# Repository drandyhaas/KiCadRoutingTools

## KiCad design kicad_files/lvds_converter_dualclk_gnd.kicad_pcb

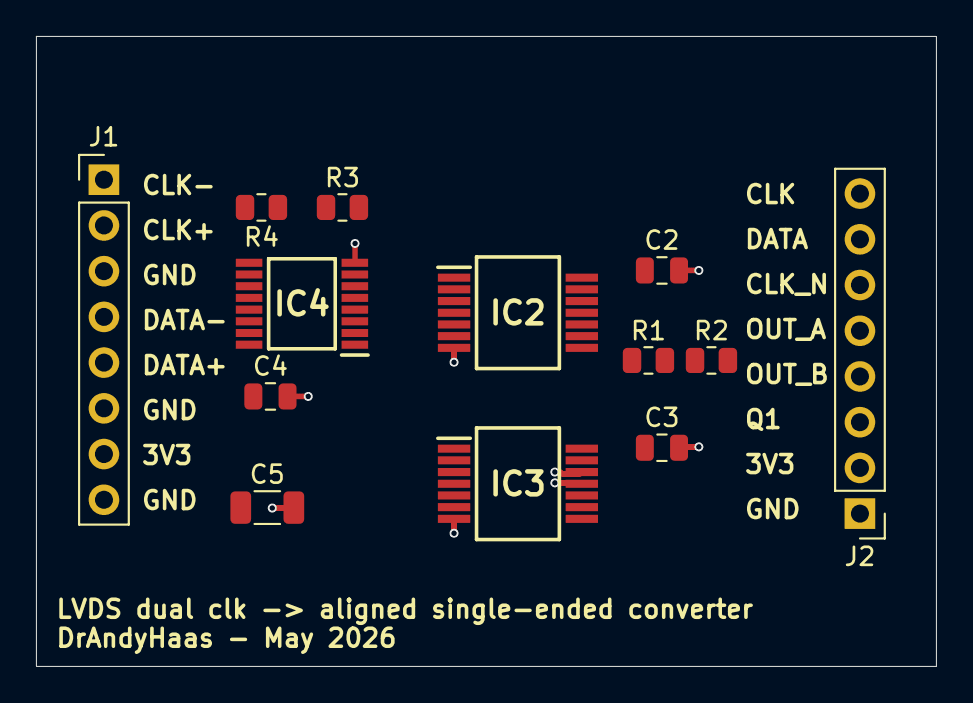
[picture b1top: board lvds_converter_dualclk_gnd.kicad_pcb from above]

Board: 2 copper layers, 50.0 x 35.0 mm, 13 parts (0 on the bottom side), 14 nets.

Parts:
C2, C3, C4: 0.1uF; C_0805_2012Metric
C5: 10uF; C_1206_3216Metric
IC2, IC3: SN74LVC74ADBR; SOP65P780X200-14N
IC4: DS90LV032ATMTCX_NOPB; SOP65P640X120-16N
J1, J2: Conn_01x08; PinHeader_1x08_P2.54mm_Vertical
R1, R2: 33; R_0805_2012Metric
R3, R4: 100; R_0805_2012Metric

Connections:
/CLK: IC3.3 (1CLK), IC4.3 (ROUT1), J2.8
/CLK+: IC4.2 (RIN1+), IC4.7 (RIN2-), J1.2, R3.1
/CLK-: IC4.1 (RIN1-), IC4.6 (RIN2+), J1.1, R3.2
/CLK_N: IC2.3 (1CLK), IC2.11 (2CLK), IC4.5 (ROUT2), J2.6
/DATA: IC2.2 (1D), IC3.2 (1D), IC4.11 (ROUT3), J2.7
/DATA+: IC4.10 (RIN3+), J1.5, R4.1
/DATA-: IC4.9 (RIN3-), J1.4, R4.2
/GND: C2.2, C3.2, C4.2, C5.2, IC2.7 (GND), IC3.7 (GND), IC3.11 (2CLK), IC3.12 (2D), IC4.8 (GND), IC4.12 (EN_2), J1.3, J1.6, J1.8, J2.1
/OUT_A: IC2.9 (2Q), R2.1
/OUT_A_R: J2.5, R2.2
/OUT_B: IC2.5 (1Q), R1.1
/OUT_B_R: J2.4, R1.2
/Q1: IC2.12 (2D), IC3.5 (1Q), J2.3
/VCC: C2.1, C3.1, C4.1, C5.1, IC2.1 (1~CLR), IC2.4 (1~PRE), IC2.10 (2~PRE), IC2.13 (2~CLR), IC2.14 (VCC), IC3.1 (1~CLR), IC3.4 (1~PRE), IC3.10 (2~PRE), IC3.13 (2~CLR), IC3.14 (VCC), IC4.4 (EN_1), IC4.16 (VCC), J1.7, J2.2

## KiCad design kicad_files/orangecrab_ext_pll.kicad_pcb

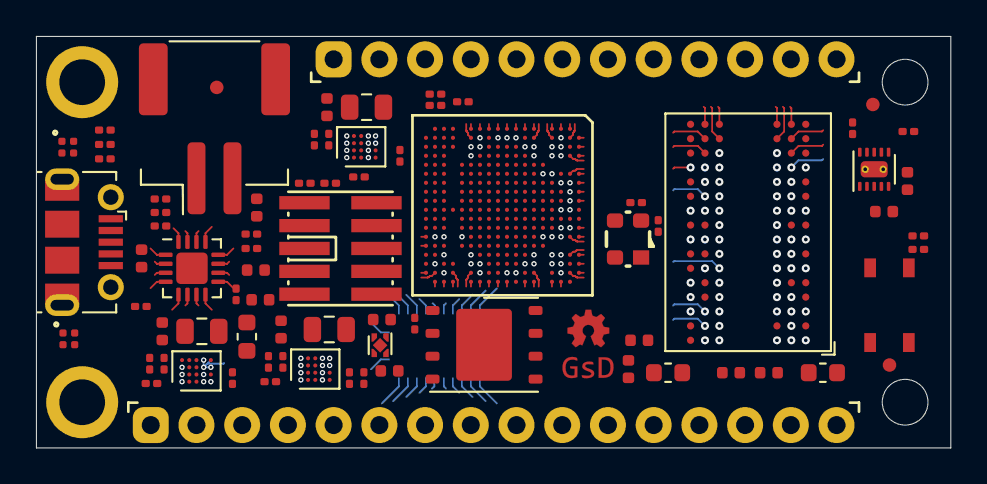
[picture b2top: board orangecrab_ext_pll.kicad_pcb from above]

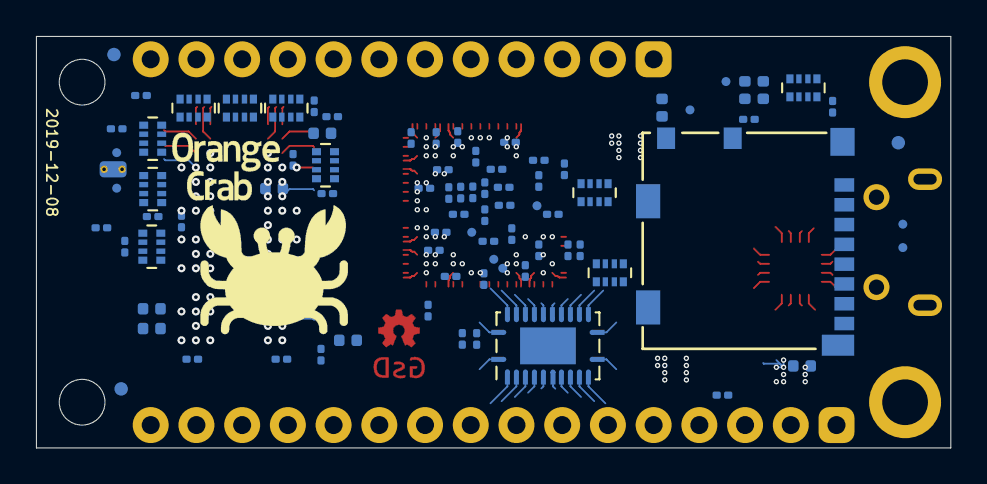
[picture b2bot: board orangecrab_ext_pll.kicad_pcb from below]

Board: 6 copper layers, 50.8 x 22.9 mm, 164 parts (83 on the bottom side), 154 nets.

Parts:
C1, C2, C5, C14, C19, C25, C27, C38, C40, C42, C44, C45, C48, C49, C52, C53, C56, C58, C60, C62, C63, C66, C67, C74, C76: 10nF; C_0201_0603Metric
C3: 10uF; C_0603_1608Metric
C4, C9, C20, C26, C28, C30, C31, C32, C33, C39, C41, C43, C50, C51, C54, C55, C57, C59, C61, C64, C65, C68, C69, C70, C71, C75: 100nF; C_0201_0603Metric
C6, C7, C8, C11, C15, C16, C17, C18, C29: 10uF; C_0402_1005Metric
C10: 0.22uF; C_0201_0603Metric
C12, C13, C46, C47, C77: 4.7uF; C_0402_1005Metric
C21, C22, C34, C35, C36, C37: 1uF; C_0402_1005Metric
C23, C24: 22uF; C_0603_1608Metric
D1, D2: LED_ARGB; 0404LED_RGB
FB1, FB2, FB3: 600R; L_0402_1005Metric
FID1, FID2, FID3, FID4, FID5, FID6: Fiducial; Fiducial_0.75mm_Mask1.5mm
H1, H2: MountingHole; MountingHole_2.2mm_M2_Pad
H3, H4: MountingHole; MountingHole_2.1mm
J1: Conn_01x12_Male; Feather_PinHeader_1x12
J2: Conn_01x16_Male; Feather_PinHeader_1x16
J3: USB_B_Micro; USB_Micro-B_Molex-105017-0001
J4: MicroSd; molex_microsd_1040310811
J5: JST; JST_PH_B2B-PH-SM4-TB_1x02-1MP_P2.00mm_Vertical
J6: JTAG; FTSH-105-XX-X-DV
L1, L2, L3: 0.47uH; L_0805_2012Metric
OSC1: KC2520B48.0000C10E00; Oscilator_2.5x2.0
R1, R5, R13, R14, R17, R18, R25: 100k; R_0201_0603Metric
R2: 31.6k; R_0201_0603Metric
R3, R6: 50R; R_0201_0603Metric
R4, R8, R23, R27, R30: 4.7k; R_0201_0603Metric
R7, R26, R28, R32, R33: 10k; R_0201_0603Metric
R9, R24: 3.57k; R_0201_0603Metric
R10: 56.2k; R_0201_0603Metric
R11: 3.06k; R_0201_0603Metric
R12: 4.32k; R_0201_0603Metric
R15: 267k; R_0201_0603Metric
R16: 147k; R_0201_0603Metric
R19: 240R; R_0402_1005Metric
R20, R22, R31: 1.5k; R_0201_0603Metric
R21, R29: 20R; R_0201_0603Metric
RN1, RN2, RN3, RN4, RN5, RN6, RN8, RN10: 50R; R_Array_Convex_4x0402
RN7, RN9: 10K; R_Array_Convex_4x0402
SW1: SW_Push; PTS_810_SMT_Switch
TP19, TP20, TP26, TP27, TP28, TP29, TP30, TP31, TP32, TP33: SMD_TP; TestPoint_Pad_D0.5mm
U1, U2, U7: FAN53541; WLCSP-20_1.934x2.434mm_Layout4x5_P0.4mm
U3: LFE5U-25F-8MG285C; csBGA_132
U4: MT41K64M16TW-107_J-TR; BGA-96_9.0x13.0mm_Layout2x3x16_P0.8mm
U5: BQ24232; QFN-16-1EP_3x3mm_P0.5mm_EP1.75x1.75mm
U6: W25Q128JVP; WSON-8-1EP_6x5mm_P1.27mm_EP3.4x4mm
U8: TPS51206; WSON-10-1EP_2x2mm_P0.4mm
U9: 74HC4067BQ; Texas_RGY_R-PVQFN-N24_EP2.05x3.1mm
U10: NCP115-2.5; Texas_X2SON-4_1x1mm_P0.65mm

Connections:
/sheetHyperRAM/RAM_VDD: C21.1, C23.1, C30.1, C32.1, C34.1, C36.1, FB2.1, U4.B2, U4.D9, U4.G7, U4.K2, U4.K8, U4.N1, U4.N9, U4.R1, U4.R9
/sheetHyperRAM/RAM_VDDQ: C22.1, C24.1, C31.1, C33.1, C35.1, C37.1, FB3.1, U4.A1, U4.A8, U4.C1, U4.C9, U4.D2, U4.E9, U4.F1, U4.H2, U4.H9
/sheetHyperRAM/RAM_ZQ: R19.1, U4.L8
/sheetIO/A0: J2.5, RN10.8, U9.8
/sheetIO/A1: J2.6, RN10.7, U9.7
/sheetIO/A2: J2.7, RN10.6, U9.6
/sheetIO/A3: J2.8, RN10.5, U9.5
/sheetIO/A4: J2.9, R6.1, U9.4
/sheetIO/A5: J2.10, R3.1, U9.3
/sheetIO/AREF: C71.1, J2.3, U9.2
/sheetIO/_USB_D_N: J3.2, R29.2, TP27.1
/sheetIO/_USB_D_P: J3.3, R21.1, TP26.1
/sheetPower/PGOOD_P1.1V: R13.1, U1.A1, U2.A2, U7.A2, U10.3
/sheetPower/PGOOD_P1.35V: R14.1, U7.A1, U8.7, U8.9
/sheetPower/PGOOD_P3.3V: R1.1, U2.A1
ADC_CTRL0: RN9.3, RN9.4, U3.G1
ADC_CTRL1: U3.F1, U9.15
ADC_MUX0: U3.F4, U9.10
ADC_MUX1: U3.F3, U9.11
ADC_MUX2: U3.F2, U9.14
ADC_MUX3: U3.H1, U9.13
ADC_SENSE_HI: RN9.7, RN9.8, U3.H3
ADC_SENSE_LO: C28.1, RN9.5, RN9.6, U3.G3
ECP5_VREF: C1.1, C4.1, C10.2, C19.1, C20.1, C25.1, C26.1, C44.2, C45.2, TP28.1, U3.B4, U3.C15, U3.H15, U4.H1, U4.M8, U8.6
EN: J1.2, R25.1, U1.A2
EXT_PLL+: TP19.1, U3.M16
EXT_PLL-: TP20.1, U3.M17
FPGA_RESET: J2.1, J6.10, U3.T15, U3.V17
GND: C1.2, C2.1, C3.1, C4.2, C5.1, C6.1, C7.1, C8.1, C9.1, C10.1, C11.1, C12.2, C13.2, C14.1, C15.1, C16.1, C17.1, C18.1, C19.2, C20.2, C21.2, C22.2, C23.2, C24.2, C25.2, C26.2, C28.2, C29.1, C30.2, C31.2, C32.2, C33.2, C34.2, C35.2, C36.2, C37.2, C38.1, C39.1, C40.1, C41.1, C42.1, C43.1, C44.1, C45.1, C46.2, C47.2, C48.2, C49.2, C50.2, C51.2, C52.2, C53.2, C54.2, C55.2, C56.2, C57.2, C58.2, C59.2, C60.2, C61.2, C62.2, C63.2, C64.2, C65.2, C66.2, C67.2, C68.2, C69.2, C70.1, C71.2, C74.2, C75.2, C76.2, C77.2, J2.4, J2.16, J3.5, J3.6, J4.6, J4.MP, J5.1, J5.MP, J6.3, J6.5, J6.7, J6.9, OSC1.2, R2.2, R9.1, R10.1, R11.1, R12.1, R15.2, R16.2, R19.2, R26.1, R27.1, R33.2, RN9.2, SW1.1, U1.B1, U1.B2, U1.B3, U1.B4, U1.C1, U1.C2, U1.C3, U1.C4, U2.B1, U2.B2, U2.B3, U2.B4, U2.C1, U2.C2, U2.C3, U2.C4, U3.B3, U3.B16, U3.E5, U3.E7, U3.E8, U3.E9, U3.E10, U3.E11, U3.E12, U3.E14, U3.F5, U3.F6, U3.F7, U3.F8, U3.F9, U3.F10, U3.F11, U3.F12, U3.F13, U3.F14, U3.G2, U3.G6, U3.G7, U3.G8, U3.G9, U3.G10, U3.G11, U3.G12, U3.G13, U3.G17, U3.H6, U3.H7, U3.H8, U3.H9, U3.H10, U3.H11, U3.H12, U3.H13, U3.J6, U3.J7, U3.J8, U3.J9, U3.J10, U3.J11, U3.J12, U3.J13, U3.K5, U3.K6, U3.K7, U3.K8, U3.K9, U3.K10, U3.K11, U3.K12, U3.K13, U3.K14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
IO_0: J2.14, U3.N17
IO_1: J2.15, U3.M18
IO_5: J1.10, U3.B10
IO_6: J1.9, U3.B9
IO_9: J1.8, U3.C8
IO_10: J1.7, U3.B8
IO_11: J1.6, U3.A8
IO_12: J1.5, U3.H2
IO_13: J1.4, U3.J2
IO_A0: RN10.1, U3.L4
IO_A1: RN10.2, U3.N3
IO_A2: RN10.3, U3.N4
IO_A3: RN10.4, U3.H4
IO_A4: R6.2, U3.G4
IO_A5: R3.2, U3.T17
IO_MISO: J2.13, U3.N15
IO_MOSI: J2.12, U3.N16
IO_SCK: J2.11, U3.R17
IO_SCL: J1.11, U3.C9
IO_SDA: J1.12, U3.C10
JTAG_TCK: J6.4, R27.2, U3.U13
JTAG_TDI: J6.8, U3.T13
JTAG_TDO: J6.6, U3.V14
JTAG_TMS: J6.2, U3.V13
LED_B: R24.1, U3.J3
LED_G: R23.1, U3.M3
LED_R: R22.1, U3.K4
unnamed: C27.1, RN6.3, RN6.4
unnamed: C29.2, C70.2, FB1.1, J4.4
unnamed: D1.2, R22.2
unnamed: D1.3, R23.2
unnamed: D1.4, R24.2
unnamed: D2.2, R8.2
unnamed: D2.3, R7.2
unnamed: L1.1, U1.D3, U1.D4, U1.E3, U1.E4
unnamed: L2.1, U2.D3, U2.D4, U2.E3, U2.E4
unnamed: L3.1, U7.D3, U7.D4, U7.E3, U7.E4
unnamed: R2.1, R5.2, U2.A3
unnamed: R7.1, U5.7
unnamed: R8.1, U5.9
unnamed: R9.2, U5.15
unnamed: R10.2, U5.14
unnamed: R11.2, U5.12
unnamed: R12.2, U5.16
unnamed: R15.1, R17.2, U1.A3
unnamed: R16.1, R18.2, U7.A3
unnamed: R26.2, U5.1
unnamed: R32.2, R33.1, U9.16
unnamed: RN9.1, U9.1
P1.1V: C15.2, C17.2, C48.1, C50.1, C52.1, C54.1, C56.1, C57.1, C58.1, C59.1, C60.1, C61.1, L1.2, R17.1, TP32.1, U1.A4, U3.D8, U3.D9, U3.D10, U3.D11, U3.J4, U3.J5, U3.J14, U3.J15, U3.M4, U3.M15, U3.P7, U3.P9, U3.P11, U9.17
P1.35V: C8.2, C16.2, C18.2, C62.1, C64.1, C66.1, C68.1, FB2.2, FB3.2, L3.2, R4.1, R18.1, TP31.1, U3.B18, U3.C6, U3.D17, U3.G5, U3.G14, U3.H5, U3.H14, U3.K15, U3.K16, U3.K17, U3.M14, U3.N14, U7.A4, U8.1, U8.2, U9.19
P2.5V: C47.1, C49.1, C51.1, C53.1, C55.1, TP30.1, U3.E6, U3.E13, U3.N6, U3.P13, U9.18, U10.1
P3.3V: C6.2, C7.2, C9.2, C46.1, C63.1, C65.1, C67.1, C69.1, C74.1, C75.1, D1.1, FB1.2, J2.2, J6.1, L2.2, OSC1.1, OSC1.4, R5.1, R28.1, R30.2, R31.2, RN7.5, RN7.6, RN7.7, RN7.8, TP29.1, U2.A4, U3.D7, U3.D12, U3.M5, U3.N5, U3.N13, U3.P14, U3.T14, U6.8, U8.10, U9.23, U9.24, U10.4
PUSB_VBUS: C77.1, J1.3, J3.1, U5.13
QSPI_D2: U3.R18, U6.3
QSPI_D3: U3.N18, U6.7
RAM_A0: RN5.6, U3.C4, U4.N3
RAM_A1: RN8.6, U3.D2, U4.P7
RAM_A2: RN5.8, U3.D3, U4.P3
RAM_A3: RN5.5, U3.A3, U4.N2
RAM_A4: RN1.7, U3.A4, U4.P8
RAM_A5: RN5.7, U3.D4, U4.P2
RAM_A6: RN1.6, U3.C3, U4.R8
RAM_A7: RN2.5, U3.B2, U4.R2
RAM_A8: RN1.5, U3.B1, U4.T8
RAM_A9: RN2.7, U3.D1, U4.R3
RAM_A10: RN8.5, U3.A7, U4.L7
RAM_A11: RN8.7, U3.C2, U4.R7
RAM_A12: RN1.8, U3.B6, U4.N7
RAM_A13: RN2.8, U3.C1, U4.T3
RAM_A14: RN8.8, U3.A2, U4.T7
RAM_A15: RN4.5, U3.C7, U4.M7
RAM_BA0: RN3.8, U3.D6, U4.M2
RAM_BA1: RN4.7, U3.B7, U4.N8
RAM_BA2: RN2.6, U3.A6, U4.M3
RAM_CAS#: RN3.5, U3.D13, U4.K3
RAM_CK+: RN6.6, U3.J18, U4.J7
RAM_CK-: RN6.5, U3.K18, U4.K7
RAM_CKE: RN4.8, U3.D18, U4.K9
RAM_CS#: RN3.6, U3.A12, U4.L2
RAM_D0: U3.C17, U4.E3
RAM_D1: U3.D15, U4.F7
RAM_D2: U3.B17, U4.F2
RAM_D3: U3.C16, U4.F8
RAM_D4: U3.A15, U4.H3
RAM_D5: U3.B13, U4.H8
RAM_D6: U3.A17, U4.G2
RAM_D7: U3.A13, U4.H7
RAM_D8: U3.F17, U4.D7
RAM_D9: U3.F16, U4.C3
RAM_D10: U3.G15, U4.C8
RAM_D11: U3.F15, U4.C2
RAM_D12: U3.J16, U4.A7
RAM_D13: U3.C18, U4.A2
RAM_D14: U3.H16, U4.B8
RAM_D15: U3.F18, U4.A3
RAM_LDM: U3.G16, U4.E7
RAM_LDQS+: U3.G18, U4.C7
RAM_LDQS-: U3.H17, U4.B7
RAM_ODT: RN6.8, U3.C13, U4.K1
RAM_RAS#: RN6.7, U3.C12, U4.J3
RAM_RESET#: U3.L18, U4.T2
RAM_UDM: U3.D16, U4.D3
RAM_UDQS+: U3.B15, U4.F3
RAM_UDQS-: U3.A16, U4.G3
RAM_WE#: RN3.7, U3.B12, U4.L3
REF_CLK: OSC1.3, U3.A9
SD0_CD: J4.9, R28.2, U3.L1
SD0_CLK: J4.5, U3.K1
SD0_CMD: J4.3, RN7.3, U3.K2
SD0_DAT0: J4.7, RN7.2, U3.J1
SD0_DAT1: J4.8, RN7.1, U3.K3
SD0_DAT2: J4.1, RN7.4, U3.L3
SD0_DAT3: J4.2, U3.M1
SPI_CONFIG_MISO: U3.T18, U6.2
SPI_CONFIG_MOSI: U3.U18, U6.5
SPI_CONFIG_SCK: R31.1, U3.U16, U6.6
SPI_CONFIG_SS: R30.1, U3.U17, U6.1
USB_D+: R20.1, R21.2, U3.N1
USB_D-: R29.1, U3.M2
USB_PULLUP: R20.2, U3.N2
USER_BUTTON: C76.1, R4.2, SW1.2, U3.J17
VBATT: C13.1, J1.1, J5.2, R32.1, U5.2, U5.3
VSYS: C2.2, C3.2, C5.2, C12.1, C14.2, D2.1, R1.2, R13.2, R14.2, R25.2, U1.D1, U1.D2, U1.E1, U1.E2, U2.D1, U2.D2, U2.E1, U2.E2, U5.5, U5.10, U5.11, U7.D1, U7.D2, U7.E1, U7.E2
VTT: C11.2, C27.2, C38.2, C39.2, C40.2, C41.2, C42.2, C43.2, RN1.1, RN1.2, RN1.3, RN1.4, RN2.1, RN2.2, RN2.3, RN2.4, RN3.1, RN3.2, RN3.3, RN3.4, RN4.1, RN4.2, RN4.3, RN4.4, RN5.1, RN5.2, RN5.3, RN5.4, RN6.1, RN6.2, RN8.1, RN8.2, RN8.3, RN8.4, TP33.1, U8.3, U8.5

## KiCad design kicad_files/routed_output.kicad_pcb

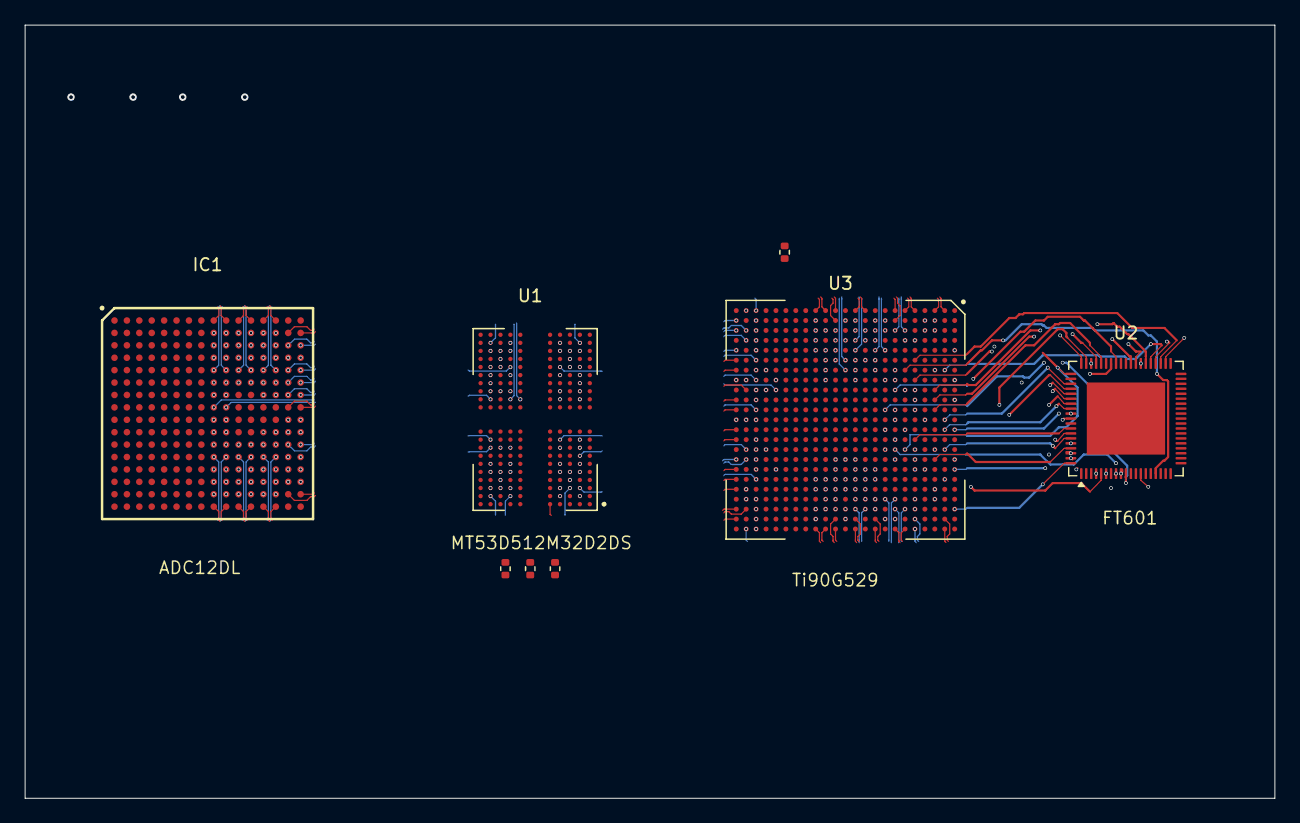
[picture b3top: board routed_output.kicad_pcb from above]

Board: 10 copper layers, 100.7 x 62.3 mm, 8 parts (0 on the bottom side), 228 nets.

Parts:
IC1: ADC12DL500ACF_Aligned; BGA256C100P16X16_1700X1700X331
R1, R2, R3, R4: 240; R_0402_1005Metric
U1: MT53D512M16D1DS_Aligned; IC_MT53D512M16D1DS-046_WT_D
U2: FT601Q_Aligned; QFN-76-1EP_9x9mm_P0.4mm_EP5.81x6.31mm
U3: Ti90G529_Functions; BGA-529_23x23_19.0x19.0mm

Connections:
/fpga_adc/VA11: IC1.E4 (VA11_1), IC1.E5 (VA11_2), IC1.E6 (VA11_3), IC1.F3 (VA11_4), IC1.F4 (VA11_5), IC1.F5 (VA11_6), IC1.F6 (VA11_7), IC1.L3 (VA11_8), IC1.L4 (VA11_9), IC1.L5 (VA11_10), IC1.L6 (VA11_11), IC1.M4 (VA11_12), IC1.M5 (VA11_13), IC1.M6 (VA11_14)
/fpga_adc/VA19: IC1.G3 (VA19_1), IC1.G4 (VA19_2), IC1.G5 (VA19_3), IC1.G6 (VA19_4), IC1.H3 (VA19_5), IC1.H4 (VA19_6), IC1.H5 (VA19_7), IC1.H6 (VA19_8), IC1.J3 (VA19_9), IC1.J4 (VA19_10), IC1.J5 (VA19_11), IC1.J6 (VA19_12), IC1.K3 (VA19_13), IC1.K4 (VA19_14), IC1.K5 (VA19_15), IC1.K6 (VA19_16)
/fpga_adc/VD11: IC1.E8 (VD11_1), IC1.F8 (VD11_2), IC1.G8 (VD11_3), IC1.K8 (VD11_4), IC1.L8 (VD11_5), IC1.M8 (VD11_6)
/fpga_adc/VLVDS: IC1.G11 (VLVDS_1), IC1.G12 (VLVDS_2), IC1.H11 (VLVDS_3), IC1.H12 (VLVDS_4), IC1.H13 (VLVDS_5), IC1.J11 (VLVDS_6), IC1.J12 (VLVDS_7), IC1.J13 (VLVDS_8), IC1.K11 (VLVDS_9), IC1.K12 (VLVDS_10)
/fpga_adc/lvds_rx1_1_N: IC1.T10 (DB0-), U3.E20 (lvds_rx1_1_N)
/fpga_adc/lvds_rx1_1_P: IC1.T9 (DB0+), U3.E21 (lvds_rx1_1)
/fpga_adc/lvds_rx1_2_N: IC1.R10 (DB1-), U3.P23 (lvds_rx1_2_N)
/fpga_adc/lvds_rx1_2_P: IC1.R9 (DB1+), U3.R23 (lvds_rx1_2)
/fpga_adc/lvds_rx1_3_N: IC1.P10 (DB2-), U3.R19 (lvds_rx1_3_N)
/fpga_adc/lvds_rx1_3_P: IC1.P9 (DB2+), U3.R18 (lvds_rx1_3)
/fpga_adc/lvds_rx1_4_N: IC1.N10 (DB3-), U3.P20 (lvds_rx1_4_N)
/fpga_adc/lvds_rx1_4_P: IC1.N9 (DB3+), U3.P21 (lvds_rx1_4)
/fpga_adc/lvds_rx1_5_N: IC1.M10 (DB4-), U3.N23 (lvds_rx1_5_N)
/fpga_adc/lvds_rx1_5_P: IC1.M9 (DB4+), U3.N22 (lvds_rx1_5)
/fpga_adc/lvds_rx1_6_N: IC1.L10 (DB5-), U3.P19 (lvds_rx1_6_N)
/fpga_adc/lvds_rx1_6_P: IC1.L9 (DB5+), U3.P18 (lvds_rx1_6)
/fpga_adc/lvds_rx1_7_N: IC1.T12 (DB6-), U3.L22 (lvds_rx1_7_N)
/fpga_adc/lvds_rx1_7_P: IC1.T11 (DB6+), U3.L23 (lvds_rx1_7)
/fpga_adc/lvds_rx1_8_N: IC1.R12 (DB7-), U3.N21 (lvds_rx1_8_N)
/fpga_adc/lvds_rx1_8_P: IC1.R11 (DB7+), U3.N20 (lvds_rx1_8)
/fpga_adc/lvds_rx1_9_N: IC1.P12 (DB8-), U3.N17 (lvds_rx1_9_N)
/fpga_adc/lvds_rx1_9_P: IC1.P11 (DB8+), U3.N16 (lvds_rx1_9)
/fpga_adc/lvds_rx1_10_N: IC1.N12 (DB9-), U3.N18 (lvds_rx1_10_N)
/fpga_adc/lvds_rx1_10_P: IC1.N11 (DB9+), U3.N19 (lvds_rx1_10)
/fpga_adc/lvds_rx1_11_N: IC1.M12 (DB10-), U3.M22 (lvds_rx1_11_N)
/fpga_adc/lvds_rx1_11_P: IC1.M11 (DB10+), U3.M21 (lvds_rx1_11)
/fpga_adc/lvds_rx1_12_N: IC1.L12 (DB11-), U3.H22 (lvds_rx1_12_N)
/fpga_adc/lvds_rx1_12_P: IC1.L11 (DB11+), U3.G22 (lvds_rx1_12)
/fpga_adc/lvds_rx1_13_N: IC1.J10 (DBSTR-), U3.M18 (lvds_rx1_13_N)
/fpga_adc/lvds_rx1_13_P: IC1.J9 (DBSTR+), U3.M19 (lvds_rx1_13)
/fpga_adc/lvds_rx2_1_N: IC1.T14 (DD0-), U3.K21 (lvds_rx2_1_N)
/fpga_adc/lvds_rx2_1_P: IC1.T13 (DD0+), U3.L21 (lvds_rx2_1)
/fpga_adc/lvds_rx2_2_N: IC1.R14 (DD1-), U3.G23 (lvds_rx2_2_N)
/fpga_adc/lvds_rx2_2_P: IC1.R13 (DD1+), U3.F23 (lvds_rx2_2)
/fpga_adc/lvds_rx2_3_N: IC1.P14 (DD2-), U3.M16 (lvds_rx2_3_N)
/fpga_adc/lvds_rx2_3_P: IC1.P13 (DD2+), U3.L16 (lvds_rx2_3)
/fpga_adc/lvds_rx2_4_N: IC1.N14 (DD3-), U3.E22 (lvds_rx2_4_N)
/fpga_adc/lvds_rx2_4_P: IC1.N13 (DD3+), U3.E23 (lvds_rx2_4)
/fpga_adc/lvds_rx2_5_N: IC1.M14 (DD4-), U3.J21 (lvds_rx2_5_N)
/fpga_adc/lvds_rx2_5_P: IC1.M13 (DD4+), U3.J20 (lvds_rx2_5)
/fpga_adc/lvds_rx2_6_N: IC1.L14 (DD5-), U3.L17 (lvds_rx2_6_N)
/fpga_adc/lvds_rx2_6_P: IC1.L13 (DD5+), U3.L18 (lvds_rx2_6)
/fpga_adc/lvds_rx2_7_N: IC1.K14 (DD6-), U3.F21 (lvds_rx2_7_N)
/fpga_adc/lvds_rx2_7_P: IC1.K13 (DD6+), U3.G21 (lvds_rx2_7)
/fpga_adc/lvds_rx2_8_N: IC1.R16 (DD7-), U3.K19 (lvds_rx2_8_N)
/fpga_adc/lvds_rx2_8_P: IC1.R15 (DD7+), U3.K20 (lvds_rx2_8)
/fpga_adc/lvds_rx2_9_N: IC1.P16 (DD8-), U3.L19 (lvds_rx2_9_N)
/fpga_adc/lvds_rx2_9_P: IC1.P15 (DD8+), U3.L20 (lvds_rx2_9)
/fpga_adc/lvds_rx2_10_N: IC1.N16 (DD9-), U3.J17 (lvds_rx2_10_N)
/fpga_adc/lvds_rx2_10_P: IC1.N15 (DD9+), U3.J18 (lvds_rx2_10)
/fpga_adc/lvds_rx2_11_N: IC1.M16 (DD10-), U3.B22 (lvds_rx2_11_N)
/fpga_adc/lvds_rx2_11_P: IC1.M15 (DD10+), U3.B23 (lvds_rx2_11)
/fpga_adc/lvds_rx2_12_N: IC1.L16 (DD11-), U3.K17 (lvds_rx2_12_N)
/fpga_adc/lvds_rx2_12_P: IC1.L15 (DD11+), U3.K18 (lvds_rx2_12)
/fpga_adc/lvds_rx2_13_N: IC1.J16 (DDSTR-), U3.G20 (lvds_rx2_13_N)
/fpga_adc/lvds_rx2_13_P: IC1.J15 (DDSTR+), U3.H20 (lvds_rx2_13)
/fpga_adc/lvds_rx3_1_N: IC1.A10 (DA0-), U3.C2 (lvds_rx3_1_N)
/fpga_adc/lvds_rx3_1_P: IC1.A9 (DA0+), U3.C3 (lvds_rx3_1)
/fpga_adc/lvds_rx3_2_N: IC1.B10 (DA1-), U3.R3 (lvds_rx3_2_N)
/fpga_adc/lvds_rx3_2_P: IC1.B9 (DA1+), U3.R2 (lvds_rx3_2)
/fpga_adc/lvds_rx3_3_N: IC1.C10 (DA2-), U3.P7 (lvds_rx3_3_N)
/fpga_adc/lvds_rx3_3_P: IC1.C9 (DA2+), U3.P8 (lvds_rx3_3)
/fpga_adc/lvds_rx3_4_N: IC1.D10 (DA3-), U3.R1 (lvds_rx3_4_N)
/fpga_adc/lvds_rx3_4_P: IC1.D9 (DA3+), U3.P1 (lvds_rx3_4)
/fpga_adc/lvds_rx3_5_N: IC1.E10 (DA4-), U3.P6 (lvds_rx3_5_N)
/fpga_adc/lvds_rx3_5_P: IC1.E9 (DA4+), U3.P5 (lvds_rx3_5)
/fpga_adc/lvds_rx3_6_N: IC1.F10 (DA5-), U3.N6 (lvds_rx3_6_N)
/fpga_adc/lvds_rx3_6_P: IC1.F9 (DA5+), U3.N5 (lvds_rx3_6)
/fpga_adc/lvds_rx3_7_N: IC1.A12 (DA6-), U3.P3 (lvds_rx3_7_N)
/fpga_adc/lvds_rx3_7_P: IC1.A11 (DA6+), U3.N3 (lvds_rx3_7)
/fpga_adc/lvds_rx3_8_N: IC1.B12 (DA7-), U3.N2 (lvds_rx3_8_N)
/fpga_adc/lvds_rx3_8_P: IC1.B11 (DA7+), U3.N1 (lvds_rx3_8)
/fpga_adc/lvds_rx3_9_N: IC1.C12 (DA8-), U3.M4 (lvds_rx3_9_N)
/fpga_adc/lvds_rx3_9_P: IC1.C11 (DA8+), U3.N4 (lvds_rx3_9)
/fpga_adc/lvds_rx3_10_N: IC1.D12 (DA9-), U3.M2 (lvds_rx3_10_N)
/fpga_adc/lvds_rx3_10_P: IC1.D11 (DA9+), U3.L2 (lvds_rx3_10)
/fpga_adc/lvds_rx3_11_N: IC1.E12 (DA10-), U3.L1 (lvds_rx3_11_N)
/fpga_adc/lvds_rx3_11_P: IC1.E11 (DA10+), U3.K1 (lvds_rx3_11)
/fpga_adc/lvds_rx3_12_N: IC1.F12 (DA11-), U3.F1 (lvds_rx3_12_N)
/fpga_adc/lvds_rx3_12_P: IC1.F11 (DA11+), U3.E1 (lvds_rx3_12)
/fpga_adc/lvds_rx3_13_N: IC1.H10 (DASTR-), U3.M7 (lvds_rx3_13_N)
/fpga_adc/lvds_rx3_13_P: IC1.H9 (DASTR+), U3.M6 (lvds_rx3_13)
/fpga_adc/lvds_rx4_1_N: IC1.A14 (DC0-), U3.K3 (lvds_rx4_1_N)
/fpga_adc/lvds_rx4_1_P: IC1.A13 (DC0+), U3.L3 (lvds_rx4_1)
/fpga_adc/lvds_rx4_2_N: IC1.B14 (DC1-), U3.J2 (lvds_rx4_2_N)
/fpga_adc/lvds_rx4_2_P: IC1.B13 (DC1+), U3.J3 (lvds_rx4_2)
/fpga_adc/lvds_rx4_3_N: IC1.C14 (DC2-), U3.L5 (lvds_rx4_3_N)
/fpga_adc/lvds_rx4_3_P: IC1.C13 (DC2+), U3.L4 (lvds_rx4_3)
/fpga_adc/lvds_rx4_4_N: IC1.D14 (DC3-), U3.H3 (lvds_rx4_4_N)
/fpga_adc/lvds_rx4_4_P: IC1.D13 (DC3+), U3.H2 (lvds_rx4_4)
/fpga_adc/lvds_rx4_5_N: IC1.E14 (DC4-), U3.G3 (lvds_rx4_5_N)
/fpga_adc/lvds_rx4_5_P: IC1.E13 (DC4+), U3.F3 (lvds_rx4_5)
/fpga_adc/lvds_rx4_6_N: IC1.F14 (DC5-), U3.L8 (lvds_rx4_6_N)
/fpga_adc/lvds_rx4_6_P: IC1.F13 (DC5+), U3.L7 (lvds_rx4_6)
/fpga_adc/lvds_rx4_7_N: IC1.G14 (DC6-), U3.J4 (lvds_rx4_7_N)
/fpga_adc/lvds_rx4_7_P: IC1.G13 (DC6+), U3.K4 (lvds_rx4_7)
/fpga_adc/lvds_rx4_8_N: IC1.B16 (DC7-), U3.J5 (lvds_rx4_8_N)
/fpga_adc/lvds_rx4_8_P: IC1.B15 (DC7+), U3.H5 (lvds_rx4_8)
/fpga_adc/lvds_rx4_9_N: IC1.C16 (DC8-), U3.L6 (lvds_rx4_9_N)
/fpga_adc/lvds_rx4_9_P: IC1.C15 (DC8+), U3.K6 (lvds_rx4_9)
/fpga_adc/lvds_rx4_10_N: IC1.D16 (DC9-), U3.J6 (lvds_rx4_10_N)
/fpga_adc/lvds_rx4_10_P: IC1.D15 (DC9+), U3.J7 (lvds_rx4_10)
/fpga_adc/lvds_rx4_11_N: IC1.E16 (DC10-), U3.C1 (lvds_rx4_11_N)
/fpga_adc/lvds_rx4_11_P: IC1.E15 (DC10+), U3.B1 (lvds_rx4_11)
/fpga_adc/lvds_rx4_12_N: IC1.F16 (DC11-), U3.F4 (lvds_rx4_12_N)
/fpga_adc/lvds_rx4_12_P: IC1.F15 (DC11+), U3.E4 (lvds_rx4_12)
/fpga_adc/lvds_rx4_13_N: IC1.H16 (DCSTR-), U3.D3 (lvds_rx4_13_N)
/fpga_adc/lvds_rx4_13_P: IC1.H15 (DCSTR+), U3.D2 (lvds_rx4_13)
/fpga_adc/lvds_rx_top_clkin1_N: IC1.K10 (DBCLK-), U3.J23 (lvds_rx_top_clkin1_N)
/fpga_adc/lvds_rx_top_clkin1_P: IC1.K9 (DBCLK+), U3.J22 (lvds_rx_top_clkin1)
/fpga_adc/lvds_rx_top_clkin2_N: IC1.K16 (DDCLK-), U3.R21 (lvds_rx_top_clkin2_N)
/fpga_adc/lvds_rx_top_clkin2_P: IC1.K15 (DDCLK+), U3.R22 (lvds_rx_top_clkin2)
/fpga_adc/lvds_rx_top_clkin3_N: IC1.G10 (DACLK-), U3.R5 (lvds_rx_bottom_clkin3_N)
/fpga_adc/lvds_rx_top_clkin3_P: IC1.G9 (DACLK+), U3.R4 (lvds_rx_bottom_clkin3)
/fpga_adc/lvds_rx_top_clkin4_N: IC1.G16 (DCCLK-), U3.G2 (lvds_rx_bottom_clkin4_N)
/fpga_adc/lvds_rx_top_clkin4_P: IC1.G15 (DCCLK+), U3.G1 (lvds_rx_bottom_clkin4)
/fpga_ddr/1V1: R3.2, R4.2
/fpga_ddr/VDD1: U1.F1 (VDD1), U1.F12 (VDD1), U1.G4 (VDD1), U1.G9 (VDD1), U1.T4 (VDD1), U1.T9 (VDD1), U1.U1 (VDD1), U1.U12 (VDD1)
/fpga_ddr/VDD2: U1.A4 (VDD2), U1.A9 (VDD2), U1.AB4 (VDD2), U1.AB9 (VDD2), U1.F5 (VDD2), U1.F8 (VDD2), U1.H1 (VDD2), U1.H5 (VDD2), U1.H8 (VDD2), U1.H12 (VDD2), U1.K1 (VDD2), U1.K3 (VDD2), U1.K10 (VDD2), U1.K12 (VDD2), U1.N1 (VDD2), U1.N3 (VDD2), U1.N10 (VDD2), U1.N12 (VDD2), U1.R1 (VDD2), U1.R5 (VDD2), U1.R8 (VDD2), U1.R12 (VDD2), U1.U5 (VDD2), U1.U8 (VDD2)
/fpga_ddr/VDDQ: U1.AA3 (VDDQ), U1.AA5 (VDDQ), U1.AA8 (VDDQ), U1.AA10 (VDDQ), U1.B3 (VDDQ), U1.B5 (VDDQ), U1.B8 (VDDQ), U1.B10 (VDDQ), U1.D1 (VDDQ), U1.D5 (VDDQ), U1.D8 (VDDQ), U1.D12 (VDDQ), U1.F3 (VDDQ), U1.F10 (VDDQ), U1.U3 (VDDQ), U1.U10 (VDDQ), U1.W1 (VDDQ), U1.W5 (VDDQ), U1.W8 (VDDQ), U1.W12 (VDDQ)
GND: IC1.A1 (AGND_1), IC1.A2 (AGND_2), IC1.A3 (AGND_3), IC1.A6 (AGND_4), IC1.A7 (AGND_5), IC1.A15 (DGND_1), IC1.A16 (DGND_2), IC1.B3 (AGND_6), IC1.B4 (AGND_7), IC1.B5 (AGND_8), IC1.B6 (AGND_9), IC1.B7 (AGND_10), IC1.C1 (AGND_11), IC1.C2 (AGND_12), IC1.C3 (AGND_13), IC1.C4 (AGND_14), IC1.C5 (AGND_15), IC1.C6 (AGND_16), IC1.C7 (AGND_17), IC1.D3 (AGND_18), IC1.D4 (AGND_19), IC1.D5 (AGND_20), IC1.D6 (AGND_21), IC1.D7 (DGND_3), IC1.E3 (AGND_22), IC1.E7 (DGND_4), IC1.F1 (AGND_23), IC1.F2 (AGND_24), IC1.F7 (DGND_5), IC1.G1 (AGND_25), IC1.G2 (AGND_26), IC1.G7 (DGND_6), IC1.H2 (AGND_27), IC1.H7 (DGND_7), IC1.H8 (DGND_8), IC1.H14 (DGND_9), IC1.J2 (AGND_28), IC1.J7 (DGND_10), IC1.J8 (DGND_11), IC1.J14 (DGND_12), IC1.K1 (AGND_29), IC1.K2 (AGND_30), IC1.K7 (DGND_13), IC1.L1 (AGND_31), IC1.L2 (AGND_32), IC1.L7 (DGND_14), IC1.M3 (AGND_33), IC1.M7 (DGND_15), IC1.N3 (AGND_34), IC1.N4 (AGND_35), IC1.N5 (AGND_36), IC1.N6 (AGND_37), IC1.N7 (DGND_16), IC1.P1 (AGND_38), IC1.P2 (AGND_39), IC1.P3 (AGND_40), IC1.P4 (AGND_41), IC1.P5 (AGND_42), IC1.P6 (AGND_43), IC1.P7 (AGND_44), IC1.R2 (AGND_45), IC1.R3 (AGND_46), IC1.R4 (AGND_47), IC1.R5 (AGND_48), IC1.R6 (AGND_49), IC1.R7 (AGND_50), IC1.T1 (AGND_51), IC1.T2 (AGND_52), IC1.T3 (AGND_53), IC1.T6 (AGND_54), IC1.T7 (AGND_55), IC1.T15 (DGND_17), IC1.T16 (DGND_18), R1.2, U1.A3 (VSS), U1.A10 (VSS), U1.AB3 (VSS), U1.AB5 (VSS), U1.AB8 (VSS), U1.AB10 (VSS), U1.C1 (VSS), U1.C5 (VSS), U1.C8 (VSS), U1.C12 (VSS), U1.D2 (VSS), U1.D4 (VSS), U1.D9 (VSS), U1.D11 (VSS), U1.E1 (VSS), U1.E5 (VSS), U1.E8 (VSS), U1.E12 (VSS), U1.G1 (VSS), U1.G3 (VSS), U1.G5 (VSS), U1.G8 (VSS), U1.G10 (VSS), U1.G12 (VSS), U1.J1 (VSS), U1.J3 (VSS), U1.J10 (VSS), U1.J12 (VSS), U1.K2 (VSS), U1.K4 (VSS), U1.K9 (VSS), U1.K11 (VSS), U1.N2 (VSS), U1.N4 (VSS), U1.N9 (VSS), U1.N11 (VSS), U1.P1 (VSS), U1.P3 (VSS), U1.P10 (VSS), U1.P12 (VSS), U1.T1 (VSS), U1.T3 (VSS), U1.T5 (VSS), U1.T8 (VSS), U1.T10 (VSS), U1.T12 (VSS), U1.V1 (VSS), U1.V5 (VSS), U1.V8 (VSS), U1.V12 (VSS), U1.W2 (VSS), U1.W4 (VSS), U1.W9 (VSS), U1.W11 (VSS), U1.Y1 (VSS), U1.Y5 (VSS), U1.Y8 (VSS), U1.Y12 (VSS), U2.1 (GND), U2.19 (GND), U2.26 (GND), U2.29 (GND), U2.36 (GND), U2.77 (GND), U3.A1 (GND), U3.A19 (GND), U3.A23 (GND), U3.AA19 (GND), U3.AB2 (GND), U3.AB5 (GND), U3.AB7 (GND), U3.AB11 (GND), U3.AB13 (GND), U3.AB17 (GND), U3.AB22 (GND), U3.AC1 (GND), U3.AC4 (GND), U3.AC9 (GND), U3.AC15 (GND), U3.AC20 (GND), U3.AC23 (GND), U3.B3 (GND), U3.B6 (GND), U3.B11 (GND), U3.B14 (GND), U3.B21 (GND), U3.D1 (GND), U3.D10 (GND), U3.D19 (GND), U3.D22 (GND), U3.F2 (GND), U3.F20 (GND), U3.F22 (GND), U3.H1 (GND), U3.H4 (GND), U3.H7 (GND), U3.H23 (GND), U3.J10 (GND)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
unnamed: U1.C3 (DMI0_A), U3.AB23 (DDR_DM[0])
unnamed: U1.Y3 (DMI0_B), U3.AA8 (DDR_DM[2])
unnamed: U1.C10 (DMI1_A), U3.AA16 (DDR_DM[1])
unnamed: U1.Y10 (DMI1_B), U3.AA3 (DDR_DM[3])
unnamed: U1.B2 (DQ0_A), U3.AA22 (DDR_DQ[0])
unnamed: U1.AA2 (DQ0_B), U3.AB9 (DDR_DQ[16])
unnamed: U1.C2 (DQ1_A), U3.AA23 (DDR_DQ[1])
unnamed: U1.Y2 (DQ1_B), U3.AA9 (DDR_DQ[17])
unnamed: U1.E2 (DQ2_A), U3.AA20 (DDR_DQ[2])
unnamed: U1.V2 (DQ2_B), U3.AC10 (DDR_DQ[18])
unnamed: U1.F2 (DQ3_A), U3.AC19 (DDR_DQ[3])
unnamed: U1.U2 (DQ3_B), U3.AA10 (DDR_DQ[19])
unnamed: U1.F4 (DQ4_A), U3.AB20 (DDR_DQ[4])
unnamed: U1.U4 (DQ4_B), U3.AC7 (DDR_DQ[20])
unnamed: U1.E4 (DQ5_A), U3.AB19 (DDR_DQ[5])
unnamed: U1.V4 (DQ5_B), U3.AA7 (DDR_DQ[21])
unnamed: U1.C4 (DQ6_A), U3.AC22 (DDR_DQ[6])
unnamed: U1.Y4 (DQ6_B), U3.AC6 (DDR_DQ[22])
unnamed: U1.B4 (DQ7_A), U3.AA21 (DDR_DQ[7])
unnamed: U1.AA4 (DQ7_B), U3.AA6 (DDR_DQ[23])
unnamed: U1.B11 (DQ8_A), U3.AA17 (DDR_DQ[8])
unnamed: U1.AA11 (DQ8_B), U3.AB4 (DDR_DQ[24])
unnamed: U1.C11 (DQ9_A), U3.AC17 (DDR_DQ[9])
unnamed: U1.Y11 (DQ9_B), U3.AA4 (DDR_DQ[25])
unnamed: U1.E11 (DQ10_A), U3.AA18 (DDR_DQ[10])
unnamed: U1.V11 (DQ10_B), U3.AC5 (DDR_DQ[26])
unnamed: U1.F11 (DQ11_A), U3.AC18 (DDR_DQ[11])
unnamed: U1.U11 (DQ11_B), U3.AA5 (DDR_DQ[27])
unnamed: U1.F9 (DQ12_A), U3.AB15 (DDR_DQ[12])
unnamed: U1.U9 (DQ12_B), U3.AB1 (DDR_DQ[28])
unnamed: U1.E9 (DQ13_A), U3.AA15 (DDR_DQ[13])
unnamed: U1.V9 (DQ13_B), U3.AA1 (DDR_DQ[29])
unnamed: U1.C9 (DQ14_A), U3.AC14 (DDR_DQ[14])
unnamed: U1.Y9 (DQ14_B), U3.AA2 (DDR_DQ[30])
unnamed: U1.B9 (DQ15_A), U3.AA14 (DDR_DQ[15])
unnamed: U1.AA9 (DQ15_B), U3.AC2 (DDR_DQ[31])
unnamed: U1.E3 (DQS0_c_A), U3.AC21 (DDR_DQS_N[0])
unnamed: U1.V3 (DQS0_c_B), U3.AC8 (DDR_DQS_N[2])
unnamed: U1.D3 (DQS0_t_A), U3.AB21 (DDR_DQS[0])
unnamed: U1.W3 (DQS0_t_B), U3.AB8 (DDR_DQS[2])
unnamed: U1.E10 (DQS1_c_A), U3.AC16 (DDR_DQS_N[1])
unnamed: U1.V10 (DQS1_c_B), U3.AC3 (DDR_DQS_N[3])
unnamed: U1.D10 (DQS1_t_A), U3.AB16 (DDR_DQS[1])
unnamed: U1.W10 (DQS1_t_B), U3.AB3 (DDR_DQS[3])
unnamed: U1.H2 (CA0_A), U1.R2 (CA0_B), U3.AC11 (DDR_A[0])
unnamed: U1.J2 (CA1_A), U1.P2 (CA1_B), U3.AA11 (DDR_A[1])
unnamed: U1.H9 (CA2_A), U1.R9 (CA2_B), U3.Y9 (DDR_A[2])
unnamed: U1.H10 (CA3_A), U1.R10 (CA3_B), U3.W9 (DDR_A[3])
unnamed: U1.H11 (CA4_A), U1.R11 (CA4_B), U3.W8 (DDR_A[4])
unnamed: U1.J11 (CA5_A), U1.P11 (CA5_B), U3.Y7 (DDR_A[5])
unnamed: U1.J4 (CKE0_A), U1.P4 (CKE0_B), U3.AA12 (DDR_CKE[0])
unnamed: U1.J9 (CK_c_A), U1.P9 (CK_c_B), U3.AB12 (DDR_CK_N)
unnamed: U1.J8 (CK_t_A), U1.P8 (CK_t_B), U3.AC12 (DDR_CK)
unnamed: U1.H4 (CS0_A), U3.Y15 (DDR_CS_N[0])
unnamed: U1.R4 (CS0_B), U3.W17 (DDR_CS_N[2])
unnamed: R3.1, U1.G2 (ODT_CA_A)
unnamed: R4.1, U1.T2 (ODT_CA_B)
unnamed: U1.T11 (RESET_n), U3.AC13 (DDR_RST_N)
unnamed: R2.1, U1.A5 (ZQ0)
unnamed: U2.4 (BE_0), U3.D17 (ftdi_be[0])
unnamed: U2.5 (BE_1), U3.C19 (ftdi_be[1])
unnamed: U2.6 (BE_2), U3.C20 (ftdi_be[2])
unnamed: U2.7 (BE_3), U3.E17 (ftdi_be[3])
unnamed: U2.58 (CLK), U3.F15 (ftdi_clk)
unnamed: U2.40 (DATA_0), U3.A5 (ftdi_data[1])
unnamed: U2.41 (DATA_1), U3.E6 (ftdi_data[2])
unnamed: U2.42 (DATA_2), U3.C7 (ftdi_data[4])
unnamed: U2.43 (DATA_3), U3.B7 (ftdi_data[3])
unnamed: U2.44 (DATA_4), U3.E8 (ftdi_data[5])
unnamed: U2.45 (DATA_5), U3.A8 (ftdi_data[6])
unnamed: U2.46 (DATA_6), U3.F9 (ftdi_data[0])
unnamed: U2.47 (DATA_7), U3.C9 (ftdi_data[7])
unnamed: U2.50 (DATA_8), U3.E9 (ftdi_data[8])
unnamed: U2.51 (DATA_9), U3.C10 (ftdi_data[10])
unnamed: U2.52 (DATA_10), U3.E10 (ftdi_data[9])
unnamed: U2.53 (DATA_11), U3.C11 (ftdi_data[13])
unnamed: U2.54 (DATA_12), U3.H11 (ftdi_data[11])
unnamed: U2.55 (DATA_13), U3.A10 (ftdi_data[12])
unnamed: U2.56 (DATA_14), U3.G11 (ftdi_data[14])
unnamed: U2.57 (DATA_15), U3.E11 (ftdi_data[16])
unnamed: U2.60 (DATA_16), U3.B12 (ftdi_data[15])
unnamed: U2.61 (DATA_17), U3.G12 (ftdi_data[17])
unnamed: U2.62 (DATA_18), U3.F13 (ftdi_data[22])
unnamed: U2.63 (DATA_19), U3.D12 (ftdi_data[18])
unnamed: U2.64 (DATA_20), U3.H13 (ftdi_data[20])
unnamed: U2.65 (DATA_21), U3.B13 (ftdi_data[21])
unnamed: U2.66 (DATA_22), U3.A13 (ftdi_data[19])
unnamed: U2.67 (DATA_23), U3.G14 (ftdi_data[23])
unnamed: U2.69 (DATA_24), U3.E14 (ftdi_data[24])
unnamed: U2.70 (DATA_25), U3.C15 (ftdi_data[26])
unnamed: U2.71 (DATA_26), U3.B15 (ftdi_data[25])
unnamed: U2.72 (DATA_27), U3.A16 (ftdi_data[27])
unnamed: U2.73 (DATA_28), U3.C16 (ftdi_data[29])
unnamed: U2.74 (DATA_29), U3.A17 (ftdi_data[28])
unnamed: U2.75 (DATA_30), U3.B18 (ftdi_data[30])
unnamed: U2.76 (DATA_31), U3.A21 (ftdi_data[31])
unnamed: U2.17 (GPIO0), U3.H8 (ftdi_gpio0)
unnamed: U2.18 (GPIO1), U3.G7 (ftdi_gpio1)
unnamed: U2.13 (~OE), U3.H15 (ftdi_oe_n)
unnamed: U2.12 (~RD), U3.E16 (ftdi_rd_n)
unnamed: U2.15 (~RESET), U3.G9 (ftdi_resetn)
unnamed: U2.9 (~RXF), U3.G15 (ftdi_rxf_n)
unnamed: U2.10 (~SIWU), U3.G8 (ftdi_siwu)
unnamed: U2.8 (~TXE), U3.E15 (ftdi_txe_n)
unnamed: U2.16 (~WAKEUP), U3.F7 (ftdi_wakeupn)
unnamed: U2.11 (~WR), U3.G16 (ftdi_wr_n)
unnamed: R1.1, U3.V8 (DDR_CAL)

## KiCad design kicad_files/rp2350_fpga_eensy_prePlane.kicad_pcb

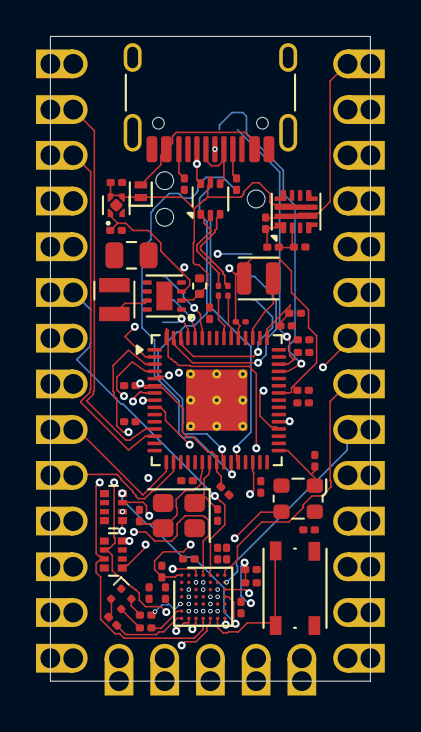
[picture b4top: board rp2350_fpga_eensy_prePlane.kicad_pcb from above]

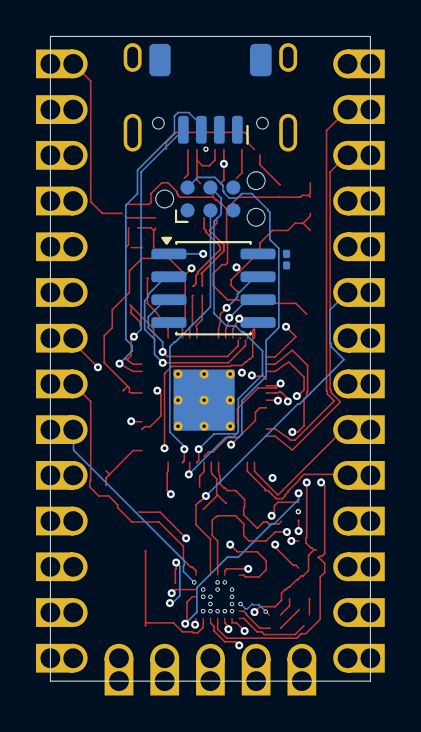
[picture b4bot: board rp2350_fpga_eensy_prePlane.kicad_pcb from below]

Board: 6 copper layers, 17.8 x 35.8 mm, 61 parts (4 on the bottom side), 74 nets.

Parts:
C1, C2, C3, C7, C8, C9, C10, C11, C12, C17, C18, C20, C21, C23, C24, C25, C28, C29, C30: 1uF; C_0201_0603Metric
C5, C13, C16, C19, C22: 4.7uF; C_0201_0603Metric
C6: 4.7uF; amemb-C_0201_0603Metric_L
C14, C15: 18pF; C_0201_0603Metric
C26: 10uF; amemb-C_0402_1005Metric_L
C27: 22uF; C_0805_2012Metric
D1: LED; LED_Wurth_150044M155260
D2: D_Schottky_Small; D_SOD-882
J1: USB_C_Receptacle_USB2.0_14P; USB_C_Receptacle_HRO_TYPE-C-31-M-12-Edge_Silkscreen_Removed
J2: Conn_ARM_SWD_TagConnect_TC2030-NL; Tag-Connect_TC2030-IDC-NL_2x03_P1.27mm_Vertical
J3: Conn_01x04_MountingPin; JST_SH_SM04B-SRSS-TB_1x04-1MP_P1.00mm_Horizontal
L1: 3.3uH; L_Wuerth_PMCI-201610
L2: 2.2uH; L_Wurth_WE-LQSH-2010
R1, R2: 5.1kR; R_0201_0603Metric
R3: 33R; R_0201_0603Metric
R4, R5: 27R; amemb-R_0201_0603Metric_L
R6: 1MR; R_0201_0603Metric
R7: 680R; R_0201_0603Metric
R8: 360R; R_0201_0603Metric
R9: 300R; R_0201_0603Metric
R11: 470kR; R_0201_0603Metric
R12: 18.7kR; R_0201_0603Metric
R13: 46.4kR; R_0201_0603Metric
RN1, RN2: 10kR; R_Array_Convex_4x0402
SW1: SKRPADE010; SW_Push_1P1T_NO_Vertical_Wuerth_434133025816
U1: APS1604M-SQR-SN; SOIC-8_3.9x4.9mm_P1.27mm
U2: T8F49I2X; amemb-WLCSP-49_3x3mm_Layout7x7_P0.4mm_Ball0.25mm
U3: USBLC6-2P6; SOT-666
U4: TPS7A2011DQN; Texas_X2SON-4_1x1mm_P0.65mm
U5: LM73100RPWR; Texas_Instruments-VQFN-HR-10_2x2mm_P0.475mm
U6: RP2354A; QFN-60-1EP_7x7mm_P0.4mm_EP3.4x3.4mm_ThermalVias
U7: TPS62162DSG; WSON-8-1EP_2x2mm_P0.5mm_EP0.9x1.6mm
U8: Teensy4.0; Teensy40
Y1: 12MHZ; Crystal_SMD_2520-4Pin_2.5x2.0mm
Y2: 32MHz; Oscillator_SMD_ECS_2520MV-xxx-xx-4Pin_2.5x2.0mm

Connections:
+1V1: C3.1, C16.1, C17.1, C18.1, U2.A1 (VCCA_PLL), U2.C4 (VCC), U2.D5 (VCC), U4.1 (OUT), U7.3 (EN)
+3V3: C2.1, C7.1, C8.1, C9.1, C10.1, C11.1, C12.1, C13.1, C19.1, C20.1, C21.1, C22.1, C23.1, C24.1, C25.1, C27.1, D1.1 (A), J2.1 (VCC), J3.2, L2.2, R3.2, RN1.5 (R4.2), RN1.6 (R3.2), RN1.7 (R2.2), RN1.8 (R1.2), RN2.5 (R4.2), RN2.8 (R1.2), U1.8 (VDD), U2.B2 (VCCIO1B), U2.B6 (VCCIO2A), U2.D1 (VCCIO1A), U2.F7 (VCCIO2B), U6.1 (IOVDD), U6.11 (IOVDD), U6.20 (IOVDD), U6.30 (IOVDD), U6.38 (IOVDD), U6.44 (ADC_AVDD), U6.45 (IOVDD), U6.49 (VREG_VIN), U6.53 (USB_OTP_VDD), U6.54 (QSPI_IOVDD), U7.6 (VOS), U8.16 (3V3), U8.31 (3V3), Y2.4 (VDD)
/PIO22: U6.34 (GPIO22), U8.4 (PIN2)
/PIO23: U6.35 (GPIO23), U8.5 (PIN3)
/Power Supply and USB/D+: R4.1, U3.1 (I/O1)
/Power Supply and USB/D-: R5.1, U3.3 (I/O2)
/RP2354A/1V1: C6.1, C28.1, C29.1, C30.1, L1.1, U6.6 (DVDD), U6.23 (DVDD), U6.39 (DVDD), U6.50 (VREG_FB)
/RP2354A/FPGA.CLK: U2.F3 (GPIOL_02_CCK), U6.4 (GPIO2)
/RP2354A/FPGA.DONE: RN2.1 (R1.1), U2.F4 (CDONE), U6.8 (GPIO5)
/RP2354A/FPGA.MOSI: U2.F2 (GPIOL_04_CDI0), U6.5 (GPIO3)
/RP2354A/FPGA.OSC_EN: R6.1, U6.31 (GPIO19), Y2.1 (Tri-State)
/RP2354A/FPGA.~CS: RN2.6 (R3.2), U2.G3 (~GPIOL_01_SS), U6.3 (GPIO1)
/RP2354A/FPGA.~RESET: RN2.7 (R2.2), U2.G4 (~CRESET), U6.7 (GPIO4)
/RP2354A/FPGA.~STATUS: U2.A4 (GPIOL_21_~STATUS), U6.9 (GPIO6)
/RP2354A/ON/OFF: U6.28 (GPIO17), U8.19 (ON/OFF)
/RP2354A/PROGRAM: U6.60 (QSPI_SS), U8.18 (PROGRAM)
/RP2354A/QSPI_PSRAM_~CS: U1.1 (~CE), U6.2 (GPIO0)
/RP2354A/RP.UART0_RX: U6.17 (GPIO13), U8.10 (PIN8)
/RP2354A/RP.UART0_TX: U6.16 (GPIO12), U8.9 (PIN7)
/RP2354A/RP.UART1_RX: U6.12 (GPIO8), U8.2 (PIN0)
/RP2354A/RP.UART1_TX: U6.13 (GPIO9), U8.3 (PIN1)
/RP2354A/SCL: J3.4, U6.43 (GPIO29/ADC3)
/RP2354A/SDA: J3.3, U6.42 (GPIO28/ADC2)
/RP2354A/SWCLK: J2.4 (SWCLK), U6.24 (SWCLK)
/RP2354A/SWDIO: J2.2 (SWDIO), U6.25 (SWDIO)
/RP2354A/USB_D+: R4.2, U6.52 (USB_DP)
/RP2354A/USB_D-: R5.2, U6.51 (USB_DM)
/T8F49I2X/B: R9.2, U2.G1 (GPIOL_05_CDI5)
/T8F49I2X/G: R8.2, U2.F1 (GPIOL_06_CDI1)
/T8F49I2X/PIN.4: U2.A5 (GPIOR_05), U8.6 (PIN4)
/T8F49I2X/PIN.5: RN1.4 (R4.1), U2.D7 (GPIOR_17_CTRL6_CBUS2), U8.7 (PIN5)
/T8F49I2X/PIN.6: RN1.3 (R3.1), U2.C7 (GPIOR_16_CTRL7_CBUS1), U8.8 (PIN6)
/T8F49I2X/PIN.9: RN1.2 (R2.1), U2.D6 (GPIOR_15_CBUS0), U8.11 (PIN9)
/T8F49I2X/PIN.10: RN1.1 (R1.1), U2.G7 (~GPIOR_37_TEST), U8.12 (PIN10)
/T8F49I2X/PIN.11: RN2.4 (R4.1), U2.G5 (GPIOR_34_CSI), U8.13 (PIN11)
/T8F49I2X/PIN.12: U2.G2 (GPIOL_03_CDI4), U8.14 (PIN12)
/T8F49I2X/PIN.13: U2.F5 (GPIOR_24), U8.20 (PIN13)
/T8F49I2X/PIN.14: U2.F6 (GPIOR_26_CBSEL0), U8.21 (PIN14)
/T8F49I2X/PIN.15: U2.E5 (GPIOR_23_CTRL4), U8.22 (PIN15)
/T8F49I2X/PIN.16: U2.C6 (GPIOR_13), U8.23 (PIN16)
/T8F49I2X/PIN.17: U2.B3 (GPIOL_16_CLK2), U8.24 (PIN17)
/T8F49I2X/PIN.18: U2.B7 (GPIOR_10), U8.25 (PIN18)
/T8F49I2X/PIN.19: U2.A7 (GPIOR_07), U8.26 (PIN19)
/T8F49I2X/PIN.20: U2.A3 (GPIOL_18_CTRL2), U8.27 (PIN20)
/T8F49I2X/PIN.21: U2.C2 (GPIOL_12_CTRL0), U8.28 (PIN21)
/T8F49I2X/PIN.22: U2.D2 (GPIOL_11_CDI3), U8.29 (PIN22)
/T8F49I2X/PIN.23: U2.E2 (GPIOL_09_CDI2), U8.30 (PIN23)
/T8F49I2X/R: R7.2, U2.E1 (GPIOL_10_CDI7)
/VIN: R11.1, U5.5 (IN), U8.33 (VIN)
GND: C1.2, C2.2, C3.2, C5.2, C6.2, C7.2, C8.2, C9.2, C10.2, C11.2, C12.2, C13.2, C14.2, C15.2, C16.2, C17.2, C18.2, C19.2, C20.2, C21.2, C22.2, C23.2, C24.2, C25.2, C26.2, C27.2, C28.2, C29.2, C30.2, J1.A1 (GND), J1.A12 (GND), J1.B1 (GND), J1.B12 (GND), J1.SH (SHIELD), J2.5 (GND), J3.1, J3.MP (MountPin), R1.2, R2.2, R6.2, R13.2, RN2.2 (R2.1), RN2.3 (R3.1), SW1.2, U1.4 (VSS), U2.A2 (GND), U2.A6 (GND), U2.B1 (GND), U2.C1 (GND), U2.C5 (GND), U2.D4 (GND), U2.E7 (GND), U3.2 (GND), U4.2 (GND), U4.5 (Pad), U5.8 (GND), U5.9 (IMON), U6.47 (VREG_PGND), U6.61 (GND), U7.1 (PGND), U7.4 (AGND), U7.5 (FB), U7.9 (PAD), U8.1 (GND), U8.17 (GND), U8.32 (GND), Y1.2 (G), Y1.4 (G), Y2.2 (GND)
unnamed: D1.4 (BK), R9.1
unnamed: D1.3 (GK), R8.1
unnamed: D1.2 (RK), R7.1
unnamed: D2.2 (A), J1.A4 (VBUS), J1.A9 (VBUS), J1.B4 (VBUS), J1.B9 (VBUS)
unnamed: C1.1, C26.1, D2.1 (K), U3.5 (VBUS), U4.3 (EN), U4.4 (IN), U5.6 (OUT), U7.2 (VIN)
unnamed: J1.A5 (CC1), R1.1
unnamed: J1.B5 (CC2), R2.1
unnamed: J1.A6 (D+), J1.B6 (D+), U3.6 (I/O1)
unnamed: J1.A7 (D-), J1.B7 (D-), U3.4 (I/O2)
unnamed: J2.3 (~RESET), U6.26 (RUN)
unnamed: U1.6 (SCLK), U6.56 (QSPI_SCLK)
unnamed: U1.3 (SIO2), U6.58 (QSPI_SD2)
unnamed: U1.7 (SIO3), U6.55 (QSPI_SD3)
unnamed: U1.5 (SI/SIO0), U6.57 (QSPI_SDO)
unnamed: U1.2 (SO/SIO1), U6.59 (QSPI_SD1)
unnamed: U2.B4 (GPIOL_20_PLLIN), Y2.3 (OUT)
unnamed: SW1.1, U2.G6 (GPIOR_35_CSO)
unnamed: R11.2, R12.1, U5.1 (EN/UVLO)
unnamed: R12.2, R13.1, U5.2 (OVLO)
unnamed: C5.1, R3.1, U6.46 (VREG_AVDD)
unnamed: L1.2, U6.48 (VREG_LX)
unnamed: C14.1, U6.21 (XIN), Y1.3
unnamed: C15.1, U6.22 (XOUT), Y1.1
unnamed: L2.1, U7.7 (SW)

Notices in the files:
kicad_files/orangecrab_ext_pll.kicad_pcb:
Licensed under CERN OHL v.1.2
